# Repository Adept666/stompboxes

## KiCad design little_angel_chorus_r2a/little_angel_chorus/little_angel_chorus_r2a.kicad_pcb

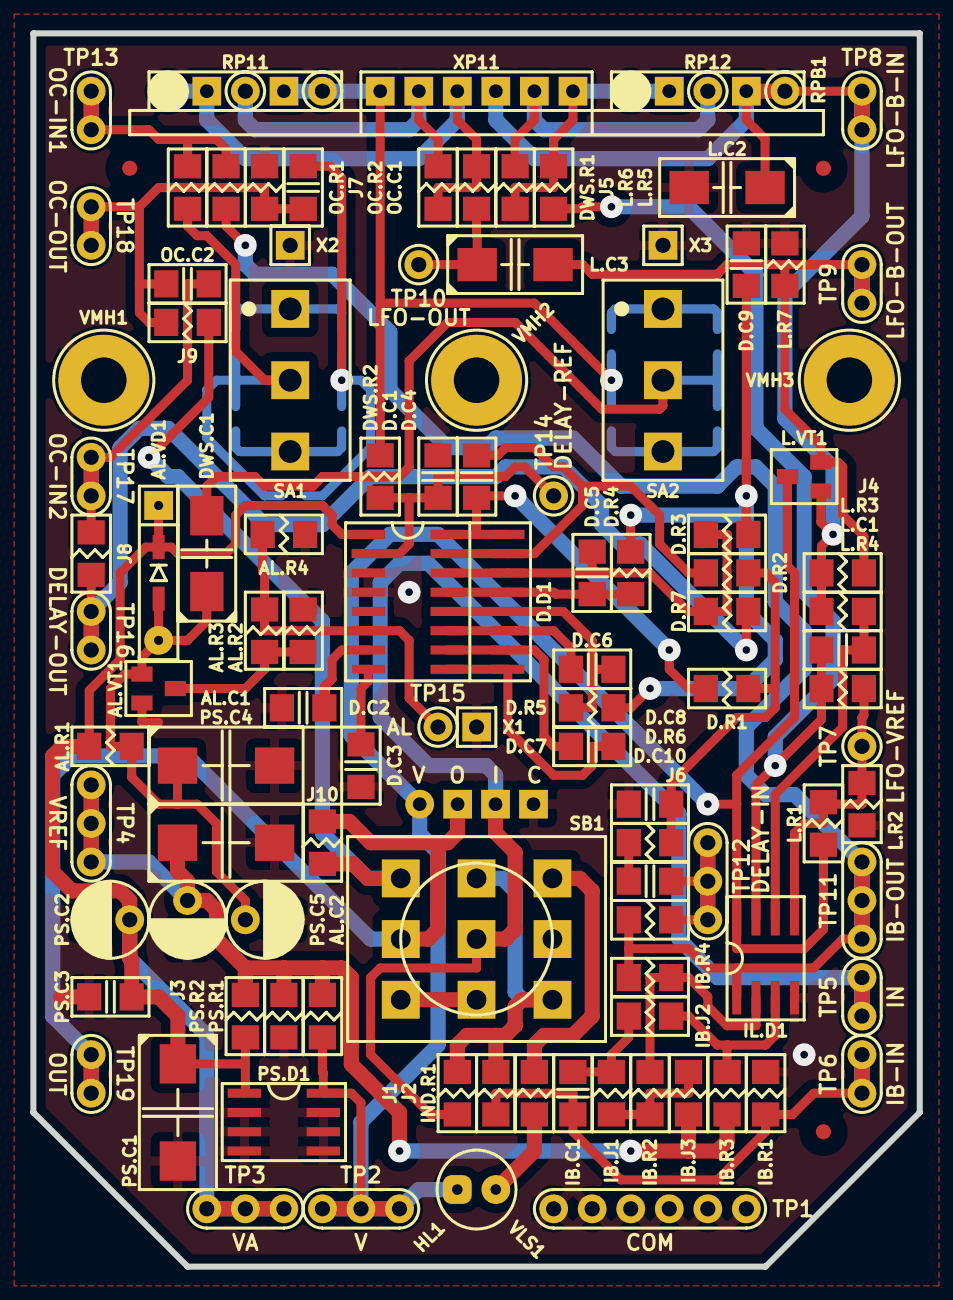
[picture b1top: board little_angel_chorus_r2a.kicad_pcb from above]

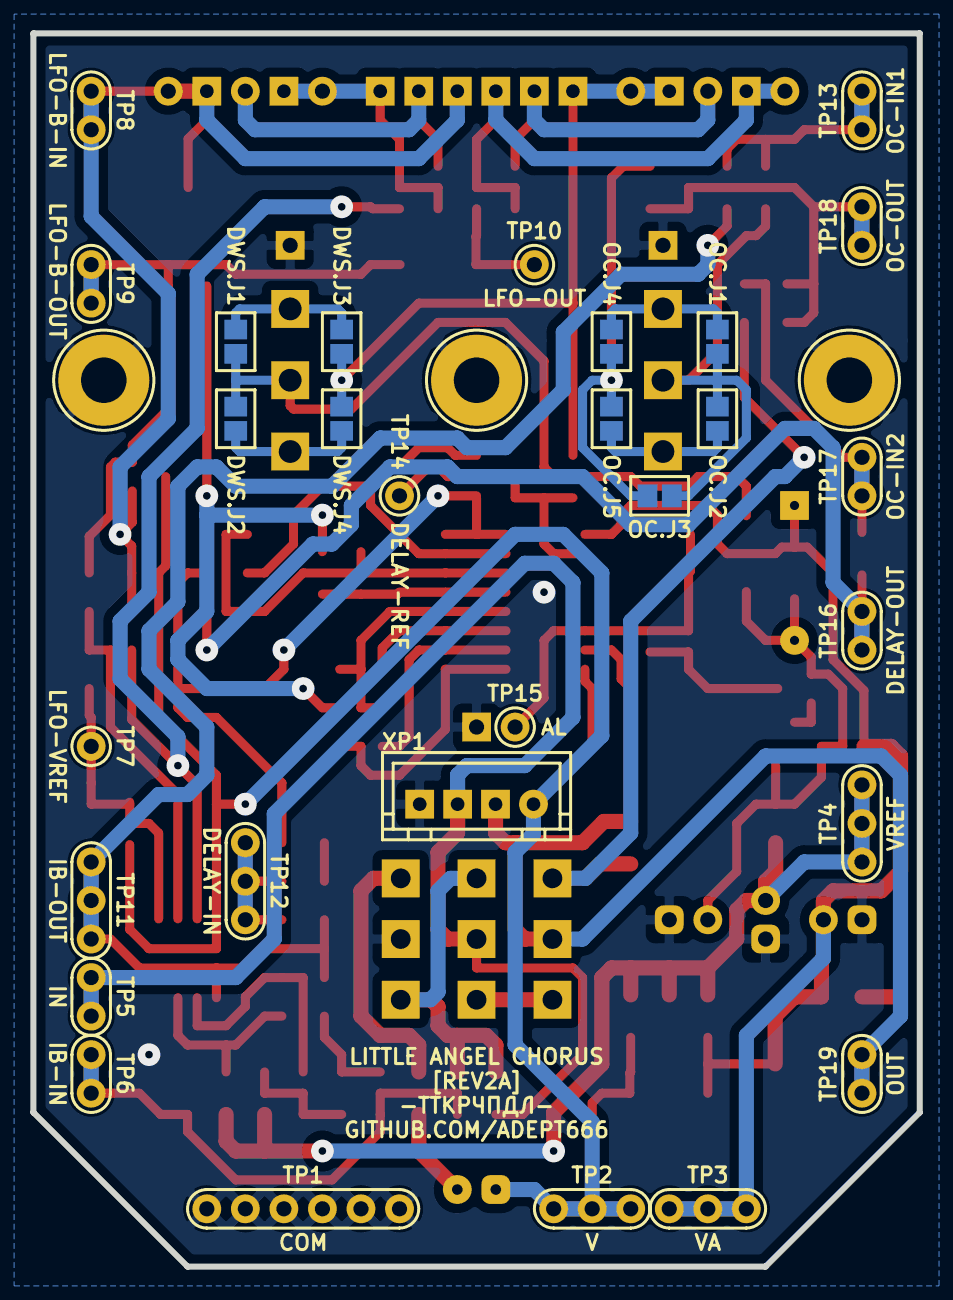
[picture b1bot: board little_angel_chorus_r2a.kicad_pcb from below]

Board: 2 copper layers, 58.4 x 81.3 mm, 118 parts (10 on the bottom side), 57 nets.

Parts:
AL.C1: 476; CP-CTSMD-D
AL.C2: 476; CP-RADIAL-D05.0-P02.0-CLS
AL.R1: 683; R-SM-1206
AL.R2: X; R-SM-1206
AL.R3: 101; R-SM-1206
AL.R4: 222; R-SM-1206
AL.VD1: 4148; P-SOD-123-OR-DO-35-V2
AL.VT1: 3904; P-SOT-23-B-E-C
D.C1: 105; C-SM-1206
D.C2, D.C3, D.C10: 104; C-SM-1206
D.C4, D.C8, D.C9: 332; C-SM-1206
D.C5: 102; C-SM-1206
D.C6, D.C7: 103; C-SM-1206
D.D1: 8970; P-SO-16-OR-SO-16W
D.R1, D.R2, D.R3, D.R4, D.R5, D.R6, D.R7: 103; R-SM-1206
DWS.C1: X; CP-CTSMD-C
DWS.J1: DWS.J1; J-SB-0805-2
DWS.J2: DWS.J2; J-SB-0805-2
DWS.J3: DWS.J3; J-SB-0805-2
DWS.J4: DWS.J4; J-SB-0805-2
DWS.R1: 0; R-SM-1206
DWS.R2: 333; R-SM-1206
HL1: FYL-5013UWC; LED-ROUND-05.0-UNI-SH-SPACER-PNL-5.3
IB.C1: 104; C-SM-1206
IB.J1: X; R-SM-1206
IB.J2, IB.J3: 0; R-SM-1206
IB.R1: 105; R-SM-1206
IB.R2, IB.R4: 223; R-SM-1206
IB.R3: 474; R-SM-1206
IL.D1: 5532; P-SO-08
IND.R1: 103; R-SM-1206
J1, J3, J4, J10: X; R-SM-1206
J2, J5, J6, J7, J8, J9: 0; R-SM-1206
L.C1: 103; C-SM-1206
L.C2, L.C3: 106; CP-CTSMD-C
L.R1: 104; R-SM-1206
L.R2: 473; R-SM-1206
L.R3, L.R4: 224; R-SM-1206
L.R5: 472; R-SM-1206
L.R6: 0; R-SM-1206
L.R7: 103; R-SM-1206
L.VT1: 3904; P-SOT-23-B-E-C
OC.C1, OC.C2: 104; C-SM-1206
OC.J1: OC.J1; J-SB-0805-2
OC.J2: OC.J2; J-SB-0805-2
OC.J3: OC.J3; J-SB-0805-2
OC.J4: OC.J4; J-SB-0805-2
OC.J5: OC.J5; J-SB-0805-2
OC.R1: 103; R-SM-1206
OC.R2: 104; R-SM-1206
PS.C1, PS.C4: 476; CP-CTSMD-D
PS.C2, PS.C5: 476; CP-RADIAL-D05.0-P02.0-CLS
PS.C3: 104; C-SM-1206
PS.D1: 78L05; P-SO-08-OUT-GND-GND-NC-NC-GND-GND-IN
PS.R1, PS.R2: 103; R-SM-1206
RPB1: B50K-B50K; RPB-1590N1-18-2x17-OR-2x1x17-1.6-PNL-7.4-2.8
SA1, SA2: X; SW-MTS-102-A2-2.5-PNL-6.0
SB1: PBS-24-302SP; SW-PBS-24-302SP-2.5-PNL-13.0
TP1: COM; TP-6-1.0-1.9
TP2: V; TP-3-1.0-1.9
TP3: VA; TP-3-1.0-1.9
TP4: VREF; TP-3-1.0-1.9
TP5: IN; TP-2-1.0-1.9
TP6: IB-IN; TP-2-1.0-1.9
TP7: LFO-VREF; TP-1-1.0-1.9
TP8: LFO-B-IN; TP-2-1.0-1.9
TP9: LFO-B-OUT; TP-2-1.0-1.9
TP10: LFO-OUT; TP-1-1.0-1.9
TP11: IB-OUT; TP-3-1.0-1.9
TP12: DELAY-IN; TP-3-1.0-1.9
TP13: OC-IN1; TP-2-1.0-1.9
TP14: DELAY-REF; TP-1-1.0-1.9
TP15: AL; TP-1-1.0-1.9
TP16: DELAY-OUT; TP-2-1.0-1.9
TP17: OC-IN2; TP-2-1.0-1.9
TP18: OC-OUT; TP-2-1.0-1.9
TP19: OUT; TP-2-1.0-1.9
VE1: 1590N1; 1590N1_A1
VFM1, VFM2, VFM3: 1.0; VFM-1.0-3.0-SL
VLS1: BR-12.7; VLS-BR
VMH1, VMH3: DI5M3x18; VMH-STA-DA5-PNL-3.0
VMH2: X; VMH-STA-DA5-PNL-3.0
X1: COM; CON-PAD-S-1.0-1.9
X2, X3: X; CON-PAD-S-1.0-1.9
XB1: 1590N1 Connector Board; XB-1590N1
XP1: B4B-XH-A; CON-XH-B4B-A

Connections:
/AL: AL.R3.2, AL.R4.2, D.D1.6, TP15.1
/CIR-IN: J1.2, J2.1, SB1.NC3, SB1.NO2
/CIR-OUT: J9.2, J10.1, SB1.NO1
/DELAY-IN: D.C10.2, J6.2, TP12.1
/DELAY-OUT: D.R7.2, J8.1, TP16.1
/DELAY-REF: D.C1.1, D.D1.2, DWS.R2.2, TP14.1
/DEPTH-IN: DWS.R1.1, J5.2, RPB1.11, RPB1.NC1
/IB-IN: IB.C1.1, IB.R1.2, J2.2, TP6.1
/IB-OUT: IB.R4.2, IL.D1.1, J6.1, J7.1, TP11.1
/IN: J1.1, SB1.COM2, TP5.1, XP1.3
/LED: IND.R1.1, SB1.NO3
/LFO-B-IN: J4.1, L.C2.+, L.R3.2, L.VT1.B, RPB1.23, RPB1.NC4, TP8.1
/LFO-B-OUT: J4.2, L.C3.-, L.R7.2, L.VT1.E, TP9.1
/LFO-OUT: J5.1, L.C3.+, TP10.1
/LFO-VREF: IL.D1.5, L.R1.1, L.R2.2, L.R4.1, TP7.1
/OC-IN1: J7.2, OC.R1.1, TP13.1
/OC-IN2: J8.2, OC.C2.1, TP17.1
/OC-OUT: J9.1, OC.C1.2, OC.C2.2, OC.R2.2, TP18.1
/OUT: J10.2, SB1.COM1, TP19.1, XP1.2
/WS: AL.C1.+, AL.C2.+, AL.R1.1, AL.VD1.A, AL.VT1.B, DWS.C1.+
COM: AL.C1.-, AL.C2.-, AL.R2.1, AL.R4.1, AL.VT1.E, D.C1.2, D.C2.1, D.C3.1, D.C8.1, D.C9.2, D.D1.3, D.D1.4, IB.R1.1, IL.D1.4, L.C2.-, L.R2.1, L.R7.1, OC.R2.1, PS.C1.-, PS.C2.-, PS.C3.2, PS.C4.-, PS.C5.-, PS.D1.GND, PS.D1.NC, PS.R2.1, SB1.COM3, TP1.1, VMH1.0, VMH2.0, VMH3.0, X1.1, X2.1, X3.1, XP1.4
unnamed: AL.R2.2, AL.R3.1, AL.VT1.C
unnamed: D.C2.2, D.D1.7
unnamed: D.C3.2, D.D1.8
unnamed: D.C4.1, D.D1.16, D.R1.1
unnamed: D.C4.2, D.D1.15, D.R2.1
unnamed: D.C5.1, D.D1.14, D.R3.1, D.R7.1
unnamed: D.C5.2, D.D1.13, D.R4.1
unnamed: D.C6.1, D.D1.12, D.R5.1
unnamed: D.C6.2, D.D1.11
unnamed: D.C7.1, D.D1.10
unnamed: D.C7.2, D.D1.9
unnamed: D.C8.2, D.R1.2, D.R2.2, D.R6.1
unnamed: D.C9.1, D.R3.2, D.R4.2, D.R5.2
unnamed: D.C10.1, D.R6.2
unnamed: DWS.C1.-, DWS.J1.1, DWS.J2.1, SA2.COM
unnamed: DWS.J1.2, DWS.J3.1, SA2.NC
unnamed: DWS.J2.2, DWS.J4.1, SA2.NO
unnamed: DWS.J3.2, DWS.J4.2, DWS.R2.1, RPB1.13, RPB1.NC2
unnamed: DWS.R1.2, RPB1.12
unnamed: HL1.C, IND.R1.2
unnamed: IB.C1.2, IB.J1.1, IB.J2.1
unnamed: IB.J1.2, IB.J3.2, IB.R2.1
unnamed: IB.J2.2, IB.R3.2, IL.D1.3
unnamed: IB.R2.2, IB.R4.1, IL.D1.2
unnamed: IL.D1.6, L.C1.1, L.R3.1
unnamed: IL.D1.7, L.C1.2, L.R4.2, L.R5.1
unnamed: L.R5.2, L.R6.1, RPB1.21, RPB1.NC3
unnamed: L.R6.2, RPB1.22
unnamed: OC.C1.1, OC.J3.2, OC.J4.2, OC.J5.2
unnamed: OC.J1.1, OC.J2.1, OC.J3.1, OC.R1.2, SA1.COM
unnamed: OC.J1.2, OC.J4.1, SA1.NC
unnamed: OC.J2.2, OC.J5.1, SA1.NO
unnamed: SB1.NC1, SB1.NC2
V: HL1.A, IL.D1.8, L.R1.2, L.VT1.C, PS.D1.IN, PS.R1.2, TP2.1, XP1.1
VA: AL.R1.2, AL.VD1.C, D.D1.1, J3.1, PS.C1.+, PS.C2.+, PS.C3.1, PS.D1.OUT, TP3.1
VREF: IB.J3.1, IB.R3.1, J3.2, PS.C4.+, PS.C5.+, PS.R1.1, PS.R2.2, TP4.1

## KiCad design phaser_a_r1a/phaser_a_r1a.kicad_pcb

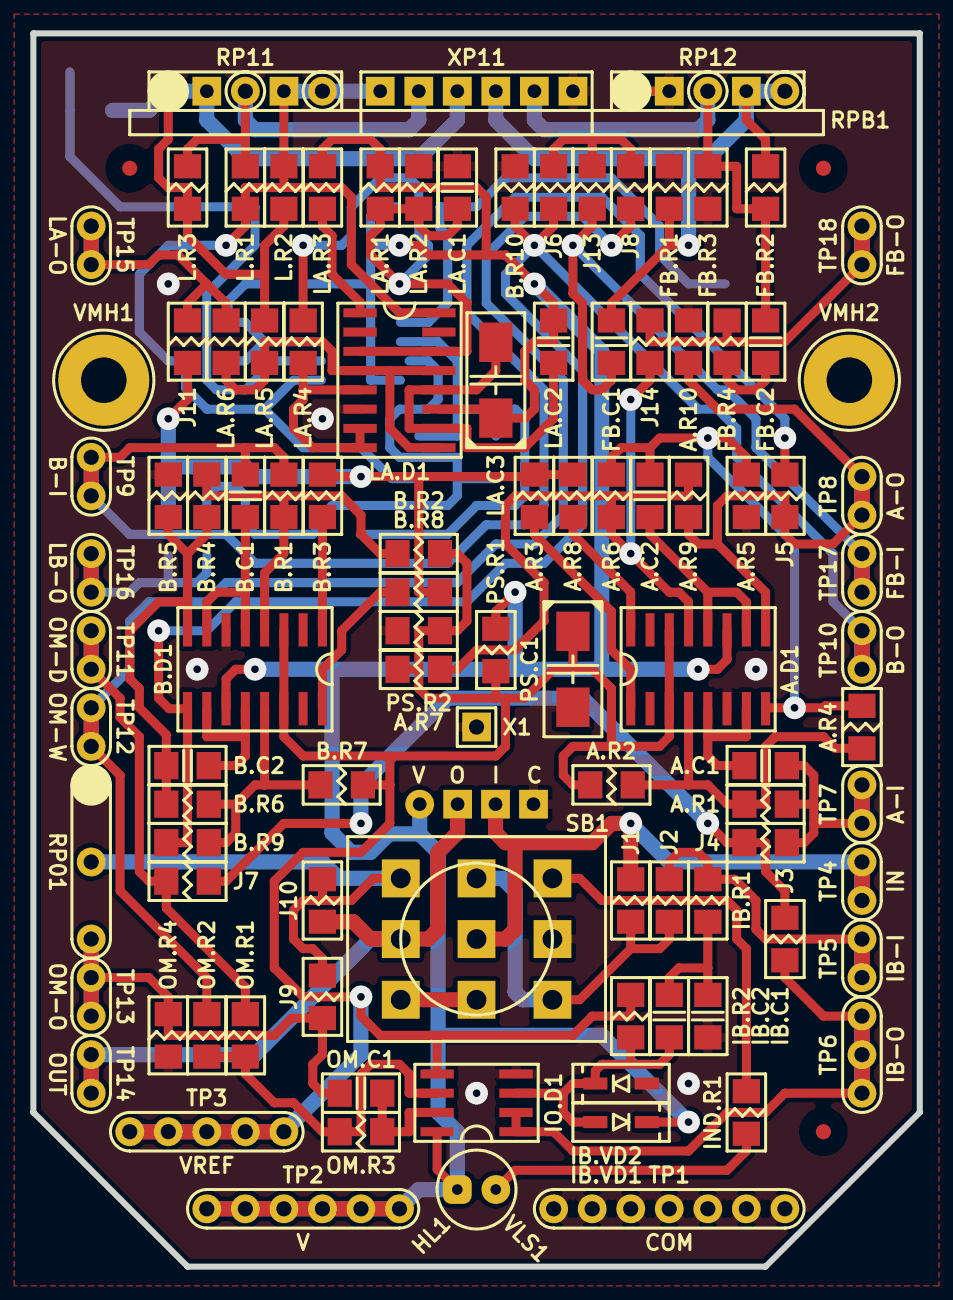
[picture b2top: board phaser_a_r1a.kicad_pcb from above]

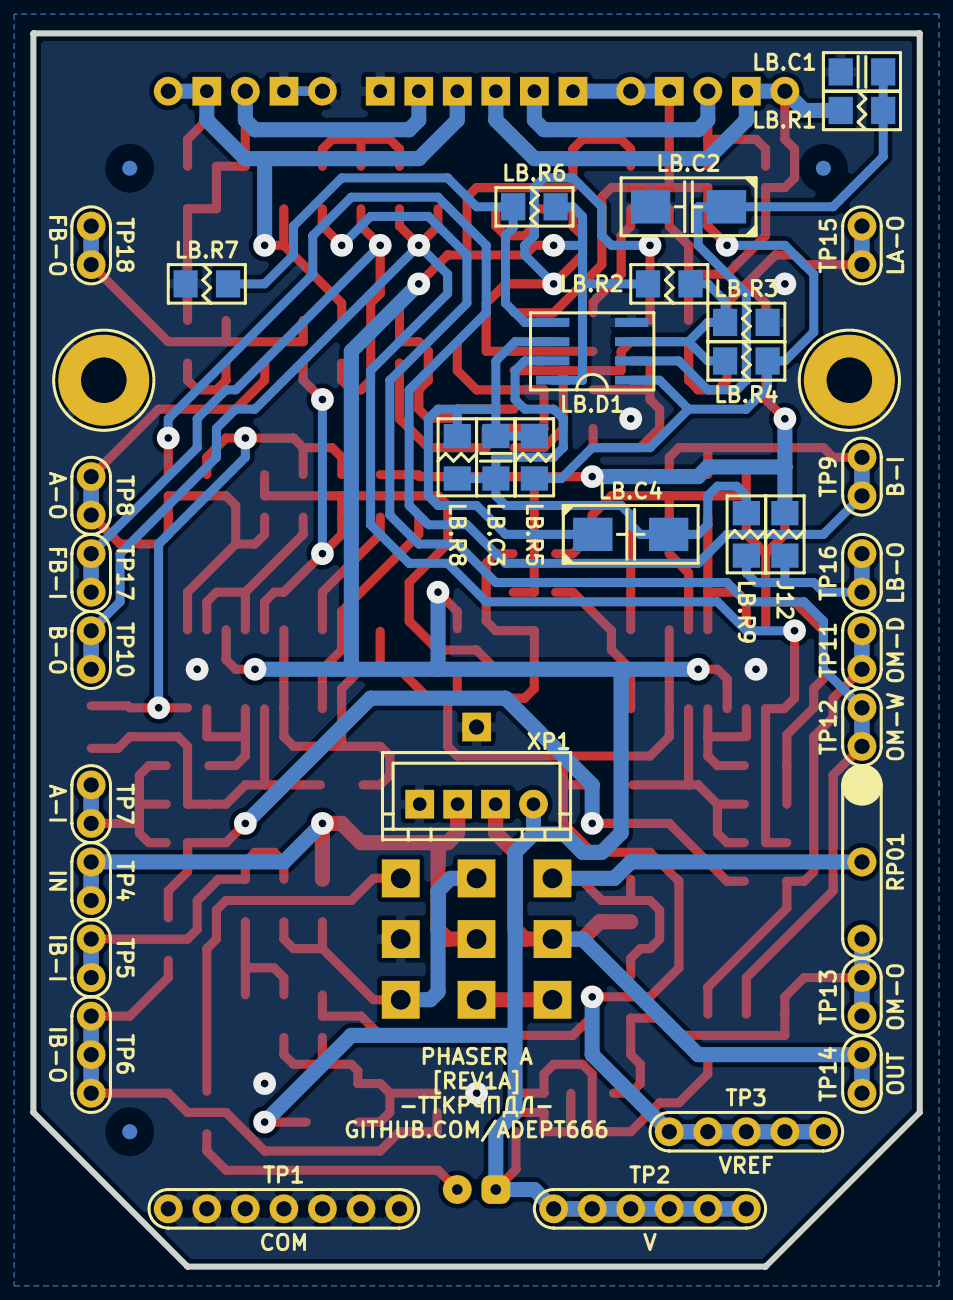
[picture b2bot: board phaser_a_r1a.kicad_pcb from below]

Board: 2 copper layers, 58.4 x 81.3 mm, 121 parts (16 on the bottom side), 60 nets.

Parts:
A.C1, A.C2: 332; C-SM-1206
A.D1: 13700; P-SO-16
A.R1, A.R4, A.R6, A.R9: 273; R-SM-1206
A.R2, A.R7: 182; R-SM-1206
A.R3, A.R8: 0; R-SM-1206
A.R5, A.R10: 103; R-SM-1206
B.C1, B.C2: 332; C-SM-1206
B.D1: 13700; P-SO-16
B.R1, B.R4, B.R6, B.R9: 273; R-SM-1206
B.R2, B.R7: 182; R-SM-1206
B.R3, B.R8: 0; R-SM-1206
B.R5, B.R10: 103; R-SM-1206
FB.C1, FB.C2: 105; C-SM-1206
FB.R1, FB.R3: X; R-SM-1206
FB.R2, FB.R4: 273; R-SM-1206
HL1: FYL-5013UWC; LED-ROUND-05.0-UNI-SH-SPACER-PNL-5.3
IB.C1: 101; C-SM-1206
IB.C2: 103; C-SM-1206
IB.R1: 102; R-SM-1206
IB.R2: 474; R-SM-1206
IB.VD1, IB.VD2: 4148; P-SOD-123
IND.R1: 103; R-SM-1206
IO.D1: 4558; P-SO-08
J1, J10, J12: X; R-SM-1206
J2, J3, J4, J5, J6, J7, J8, J9, J11, J13, J14: 0; R-SM-1206
L.R1, L.R2: X; R-SM-1206
L.R3: 0; R-SM-1206
LA.C1: 473; C-SM-1206
LA.C2: 335; C-SM-1206
LA.C3: X; CP-CTSMD-C
LA.D1: 13700; P-SO-16
LA.R1, LA.R3: 274; R-SM-1206
LA.R2: 104; R-SM-1206
LA.R4, LA.R6: 103; R-SM-1206
LA.R5: 472; R-SM-1206
LB.C1, LB.C3: X; C-SM-1206
LB.C2, LB.C4: X; CP-CTSMD-C
LB.D1: X; P-SO-08
LB.R1, LB.R2, LB.R3, LB.R4, LB.R5, LB.R6, LB.R7, LB.R8, LB.R9: X; R-SM-1206
OM.C1: 105; C-SM-1206
OM.R1, OM.R2: 273; R-SM-1206
OM.R3: 153; R-SM-1206
OM.R4: 154; R-SM-1206
PS.C1: 106; CP-CTSMD-C
PS.R1, PS.R2: 103; R-SM-1206
RP01: X; RP-EXTERNAL
RPB1: C500K-C500K; RPB-1590N1-18-2x17-OR-2x1x17-1.6-PNL-7.4-2.8
SB1: PBS-24-302SP; SW-PBS-24-302SP-2.5-PNL-13.0
TP1: COM; TP-7-1.0-1.9
TP2: V; TP-6-1.0-1.9
TP3: VREF; TP-5-1.0-1.9
TP4: IN; TP-2-1.0-1.9
TP5: IB-I; TP-2-1.0-1.9
TP6: IB-O; TP-3-1.0-1.9
TP7: A-I; TP-2-1.0-1.9
TP8: A-O; TP-2-1.0-1.9
TP9: B-I; TP-2-1.0-1.9
TP10: B-O; TP-2-1.0-1.9
TP11: OM-D; TP-2-1.0-1.9
TP12: OM-W; TP-2-1.0-1.9
TP13: OM-O; TP-2-1.0-1.9
TP14: OUT; TP-2-1.0-1.9
TP15: LA-O; TP-2-1.0-1.9
TP16: LB-O; TP-2-1.0-1.9
TP17: FB-I; TP-2-1.0-1.9
TP18: FB-O; TP-2-1.0-1.9
VE1: 1590N1; 1590N1_A1
VFM1, VFM2, VFM3: 1.0; VFM-1.0-3.0-DL
VLS1: BR-12.7; VLS-BR
VMH1, VMH2: DI5M3x18; VMH-STA-DA5-PNL-3.0
X1: COM; CON-PAD-S-1.0-1.9
XB1: 1590N1 Connector Board; XB-1590N1
XP1: B4B-XH-A; CON-XH-B4B-A

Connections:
/A-IN: A.C1.1, A.R1.1, J4.2, TP7.1
/A-OUT: A.D1.9, A.R9.2, A.R10.1, J5.1, TP8.1
/B-IN: B.C1.1, B.R1.1, J5.2, TP9.1
/B-OUT: B.D1.9, B.R9.2, B.R10.1, J6.1, TP10.1
/CIR-IN: J1.2, J2.1, SB1.NC3, SB1.NO2
/CIR-OUT: J9.2, J10.1, RP01.2, SB1.NO1
/DRY: J3.2, J4.1, J7.1
/FB: A.D1.13, A.R6.2, A.R7.1, A.R9.1, J14.2
/FB-IN: FB.C1.1, J13.2, TP17.1
/FB-OUT: FB.R4.2, J14.1, TP18.1
/IB-IN: IB.R1.1, J2.2, TP5.1
/IB-OUT: IO.D1.1, IO.D1.2, J3.1, TP6.1
/IN: J1.1, SB1.COM2, TP4.1, XP1.3
/LED: IND.R1.1, SB1.NO3
/LFO: A.R3.1, A.R8.1, B.R3.1, B.R8.1, J11.2, J12.2
/LFOA-OUT: J11.1, LA.R6.2, TP15.1
/LFOB-OUT: J12.1, LB.R9.2, TP16.1
/OM-INDRY: J7.2, OM.R1.2, TP11.1
/OM-INWET: J8.2, OM.R2.1, TP12.1
/OM-OUT: J9.1, OM.C1.2, OM.R4.2, RP01.3, TP13.1
/OUT: J10.2, SB1.COM1, TP14.1, XP1.2
/RP11-1: L.R2.2, L.R3.2, LA.R5.1, LB.R1.2, RPB1.11, RPB1.NC1
/RP11-2: L.R1.2, L.R3.1, RPB1.12
/RP11-3: L.R1.1, L.R2.1, LA.D1.16, LB.D1.1, LB.R4.2, LB.R5.1, RPB1.13, RPB1.NC2
/WET: J6.2, J8.1, J13.1
COM: A.D1.6, A.R5.2, A.R10.2, B.D1.6, B.R5.2, B.R10.2, FB.R1.1, FB.R3.1, IB.C1.2, IB.VD2.A, IO.D1.4, LA.C1.2, LA.D1.6, LA.R2.1, LB.C1.1, LB.C2.-, LB.D1.4, LB.R3.1, LB.R7.1, OM.R4.1, PS.C1.-, PS.R2.1, RP01.1, RPB1.21, RPB1.NC3, SB1.COM3, TP1.1, VMH1.0, VMH2.0, X1.1, XP1.4
unnamed: A.C1.2, A.D1.5, A.D1.7
unnamed: A.C2.1, A.D1.8, A.R4.2, A.R5.1, A.R6.1
unnamed: A.C2.2, A.D1.10, A.D1.12
unnamed: A.D1.1, A.R3.2
unnamed: A.D1.4, A.R1.2, A.R2.1, A.R4.1
unnamed: A.D1.16, A.R8.2
unnamed: B.C1.2, B.D1.5, B.D1.7
unnamed: B.C2.1, B.D1.8, B.R4.2, B.R5.1, B.R6.1
unnamed: B.C2.2, B.D1.10, B.D1.12
unnamed: B.D1.1, B.R3.2
unnamed: B.D1.4, B.R1.2, B.R2.1, B.R4.1
unnamed: B.D1.13, B.R6.2, B.R7.1, B.R9.1
unnamed: B.D1.16, B.R8.2
unnamed: FB.C1.2, FB.R1.2, FB.R2.2, RPB1.23, RPB1.NC4
unnamed: FB.C2.1, FB.R2.1, FB.R3.2, RPB1.22
unnamed: FB.C2.2, FB.R4.1
unnamed: HL1.C, IND.R1.2
unnamed: IB.C1.1, IB.C2.1, IB.R1.2
unnamed: IB.C2.2, IB.R2.2, IB.VD1.A, IB.VD2.C, IO.D1.3
unnamed: IO.D1.6, OM.R1.1, OM.R2.2, OM.R3.1
unnamed: IO.D1.7, OM.C1.1, OM.R3.2
unnamed: LA.C1.1, LA.D1.3, LA.D1.14, LA.R1.1, LA.R2.2, LA.R4.1
unnamed: LA.C2.2, LA.C3.-, LA.D1.10, LA.D1.12
unnamed: LA.D1.1, LA.R3.1
unnamed: LA.D1.5, LA.D1.7, LA.D1.8, LA.R4.2
unnamed: LA.D1.4, LA.D1.9, LA.D1.13, LA.R5.2, LA.R6.1
unnamed: LB.C1.2, LB.C2.+, LB.D1.2, LB.R1.1
unnamed: LB.C3.1, LB.C4.+, LB.D1.6, LB.R5.2, LB.R8.1
unnamed: LB.C3.2, LB.C4.-, LB.D1.7, LB.R8.2, LB.R9.1
unnamed: LB.D1.3, LB.R2.2, LB.R3.2, LB.R4.1
unnamed: LB.D1.5, LB.R6.1, LB.R7.2
unnamed: SB1.NC1, SB1.NC2
V: A.D1.11, B.D1.11, HL1.A, IB.VD1.C, IO.D1.8, LA.C2.1, LA.C3.+, LA.D1.11, LA.R1.2, LA.R3.2, LB.D1.8, LB.R2.1, LB.R6.2, PS.R1.2, TP2.1, XP1.1
VREF: A.D1.3, A.D1.14, A.R2.2, A.R7.2, B.D1.3, B.D1.14, B.R2.2, B.R7.2, IB.R2.1, IO.D1.5, PS.C1.+, PS.R1.1, PS.R2.2, TP3.1

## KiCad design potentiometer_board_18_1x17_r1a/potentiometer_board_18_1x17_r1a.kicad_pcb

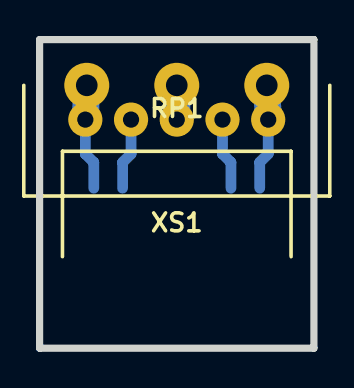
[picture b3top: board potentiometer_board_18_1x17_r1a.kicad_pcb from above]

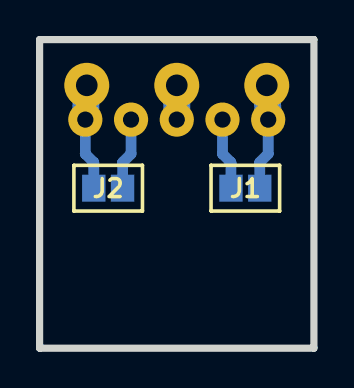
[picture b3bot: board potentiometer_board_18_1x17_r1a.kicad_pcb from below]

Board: 2 copper layers, 15.2 x 17.1 mm, 4 parts (2 on the bottom side), 5 nets.

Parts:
J1: J1; J-SB-0805-2
J2: J2; J-SB-0805-2
RP1: 16/17; RP-PDB181-K-20-P-CIRCULAR
XS1: PBS-05R; CON-PBS-05R-CIRCULAR

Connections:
unnamed: J1.1, RP1.3, XS1.1
unnamed: J1.2, XS1.2
unnamed: J2.1, XS1.4
unnamed: J2.2, RP1.1, XS1.5
unnamed: RP1.2, XS1.3

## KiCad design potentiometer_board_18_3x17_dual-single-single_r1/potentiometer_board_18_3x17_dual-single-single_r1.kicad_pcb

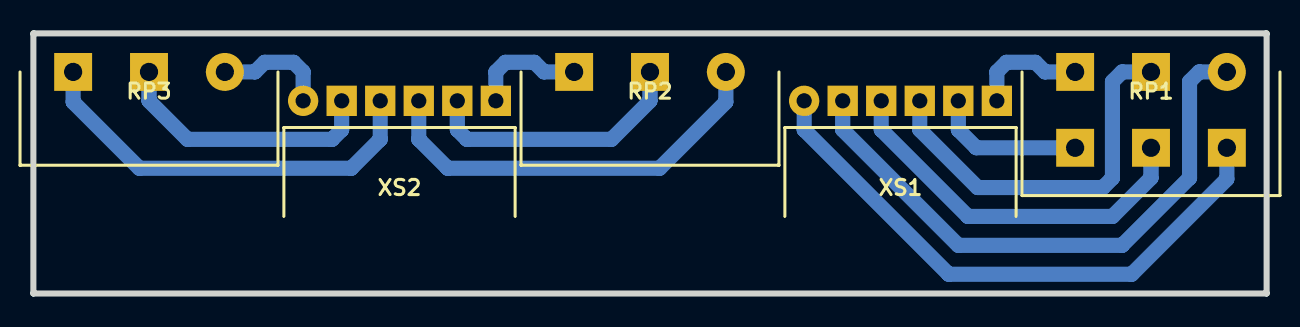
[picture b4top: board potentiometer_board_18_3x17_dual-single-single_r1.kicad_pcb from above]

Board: 2 copper layers, 81.3 x 17.1 mm, 5 parts (0 on the bottom side), 12 nets.

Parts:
RP1: RP1: DUAL 16/17; RP-PDB182-K-20-P
RP2: RP2: 16/17; RP-PDB181-K-20-P
RP3: RP3: 16/17; RP-PDB181-K-20-P
XS1, XS2: PBS-06R; CON-PBS-06R

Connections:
unnamed: RP1.1, XS1.2
unnamed: RP1.2, XS1.4
unnamed: RP1.3, XS1.6
unnamed: RP1.4, XS1.1
unnamed: RP1.5, XS1.3
unnamed: RP1.6, XS1.5
unnamed: RP2.1, XS2.4
unnamed: RP2.2, XS2.5
unnamed: RP2.3, XS2.6
unnamed: RP3.1, XS2.1
unnamed: RP3.2, XS2.2
unnamed: RP3.3, XS2.3

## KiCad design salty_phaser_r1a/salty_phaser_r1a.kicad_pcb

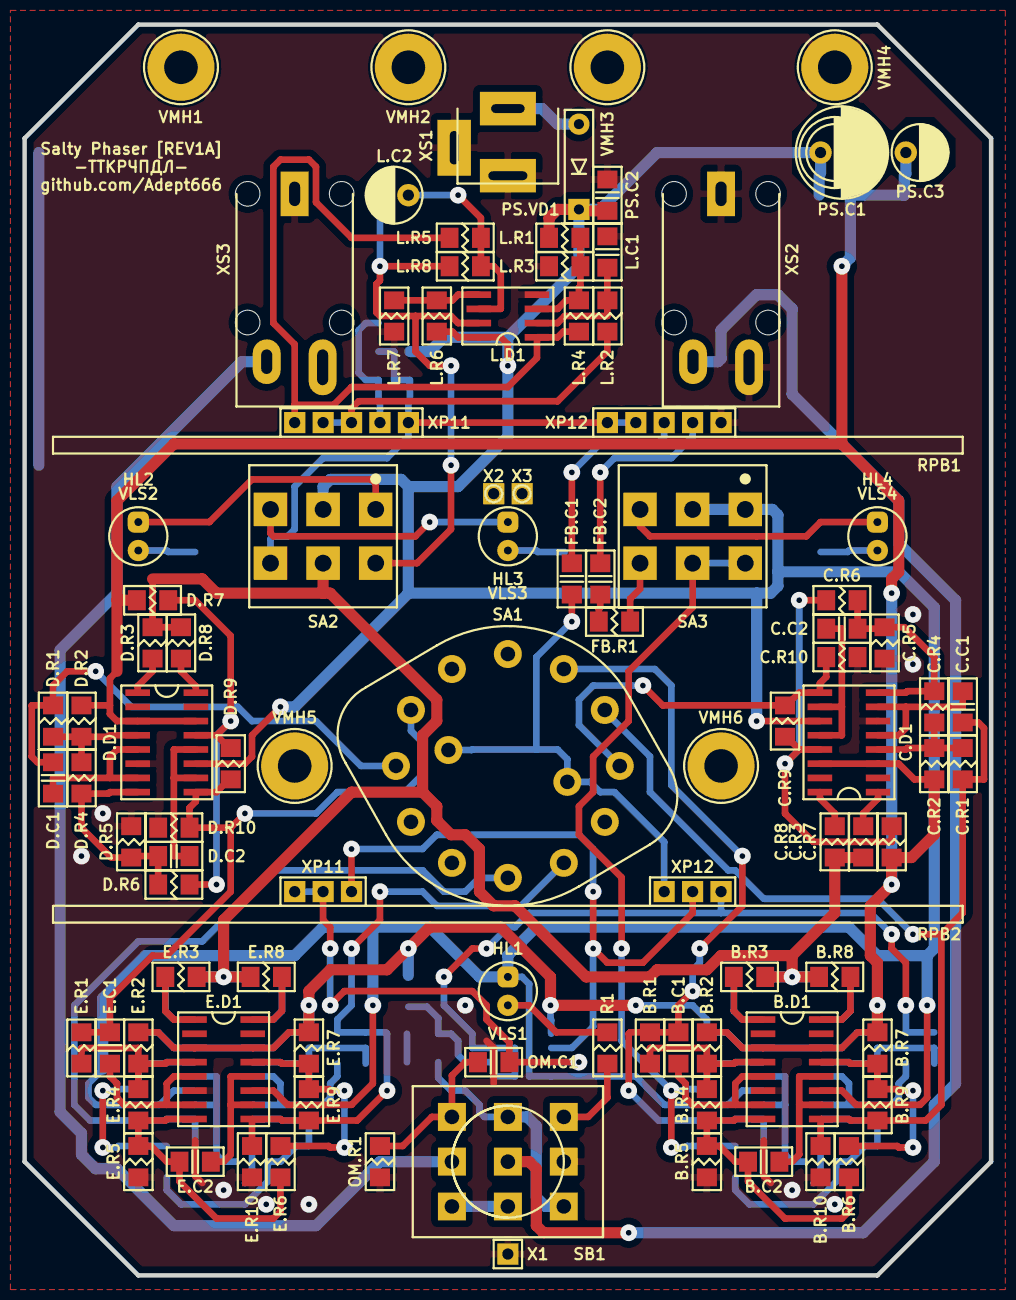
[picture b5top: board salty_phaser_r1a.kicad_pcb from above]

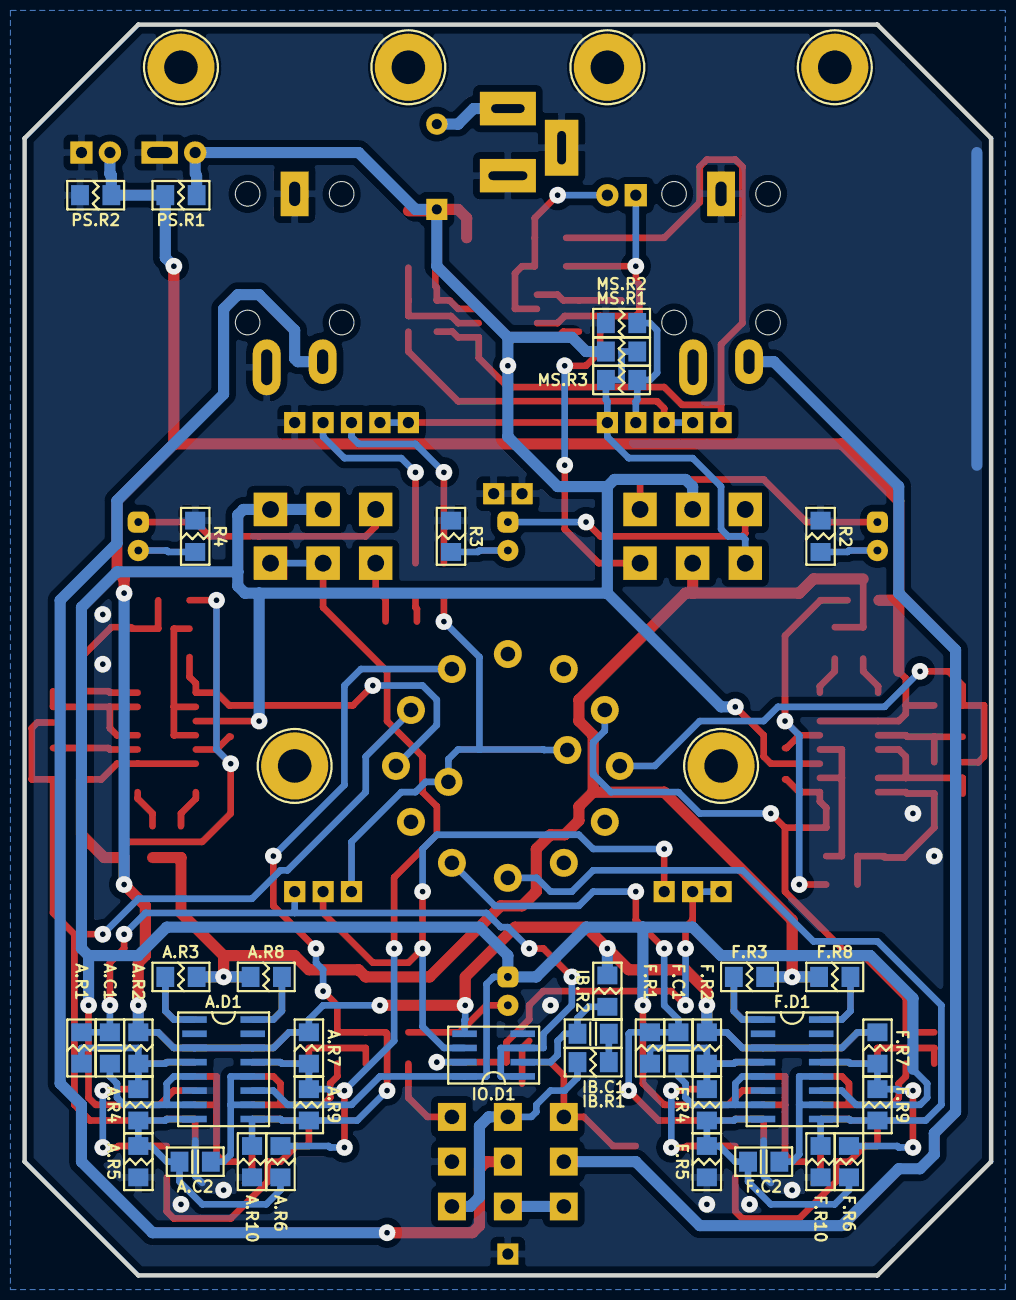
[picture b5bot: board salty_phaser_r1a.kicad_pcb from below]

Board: 2 copper layers, 86.4 x 111.8 mm, 138 parts (38 on the bottom side), 85 nets.

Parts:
A.C1, A.C2: X; C-SM-1206
A.D1: X; P-SO-16
A.R1, A.R2, A.R3, A.R4, A.R5, A.R6, A.R7, A.R8, A.R9, A.R10: X; R-SM-1206
B.C1, B.C2: X; C-SM-1206
B.D1: X; P-SO-16
B.R1, B.R2, B.R3, B.R4, B.R5, B.R6, B.R7, B.R8, B.R9, B.R10: X; R-SM-1206
C.C1, C.C2: 332; C-SM-1206
C.D1: 13700; P-SO-16
C.R1, C.R4, C.R6, C.R9: 273; R-SM-1206
C.R2, C.R7: 182; R-SM-1206
C.R3, C.R5, C.R8, C.R10: 103; R-SM-1206
D.C1, D.C2: 332; C-SM-1206
D.D1: 13700; P-SO-16
D.R1, D.R4, D.R6, D.R9: 273; R-SM-1206
D.R2, D.R7: 182; R-SM-1206
D.R3, D.R5, D.R8, D.R10: 103; R-SM-1206
E.C1, E.C2: X; C-SM-1206
E.D1: X; P-SO-16
E.R1, E.R2, E.R3, E.R4, E.R5, E.R6, E.R7, E.R8, E.R9, E.R10: X; R-SM-1206
F.C1, F.C2: X; C-SM-1206
F.D1: X; P-SO-16
F.R1, F.R2, F.R3, F.R4, F.R5, F.R6, F.R7, F.R8, F.R9, F.R10: X; R-SM-1206
FB.C1, FB.C2: X; C-SM-1206
FB.R1: X; R-SM-1206
HL1: FYL-5013UWC; LED-ROUND-05.0-UNI-SH-SPACER-PNL-5.3
HL2, HL3, HL4: X; LED-ROUND-05.0-UNI-SH-SPACER-PNL-5.3
IB.C1: 472; C-SM-1206
IB.R1: 103; R-SM-1206
IB.R2: 105; R-SM-1206
IO.D1: 4558; P-SO-08
L.C1: 474; C-SM-1206
L.C2: 475; CP-RADIAL-D05.0-P02.0-CLS
L.D1: 4558; P-SO-08
L.R1, L.R3, L.R4: 364; R-SM-1206
L.R2: 154; R-SM-1206
L.R5, L.R6, L.R8: 103; R-SM-1206
L.R7: 622; R-SM-1206
MS.R1: 331; R-SM-1206
MS.R2: 680; R-SM-1206
MS.R3: 470; R-SM-1206
OM.C1: 473; C-SM-1206
OM.R1: X; R-SM-1206
PS.C1: 107; CP-RADIAL-D05.0-P02.0-CLS-OR-D06.3-P02.5-OR-D08.0-P03.5-CLS
PS.C2: 104; C-SM-1206
PS.C3: 106; CP-RADIAL-D05.0-P02.0-CLS
PS.R1, PS.R2: 103; R-SM-1206
PS.VD1: 5817; P-DO-41
R1: 103; R-SM-1206
R2, R3, R4: X; R-SM-1206
RPB1: B500K-A1K-B100K; RPB-1590BB-18-3x17-1.5-PNL-7.4-2.8
RPB2: X; RPB-1590BB-18-2x17-1.5-PNL-7.4-2.8
SA1: X; SW-RBS-1-2P6W-VP-PNL-9.5
SA2: MTS-202-A2; SW-MTS-202-A2-3.0-PNL-6.0
SA3: X; SW-MTS-202-A2-3.0-PNL-6.0
SB1: PBS-24-302SP; SW-PBS-24-302SP-2.5-PNL-13.0
VE1: 1590BB; 1590BB_B1
VLS1: BR-12.7; VLS-BR
VLS2, VLS3, VLS4: X; VLS-BR
VMH1, VMH2, VMH3, VMH4, VMH5, VMH6: DI5M3x18; VMH-STA-DA5-PNL-3.0
X1, X2: COM; CON-PAD-S-1.0-1.9
X3: X; CON-PAD-S-1.0-1.9
XS1: DC-005; CON-DC-005
XS2, XS3: PJ-309; CON-ST-008X-04-OR-ST-008X-05

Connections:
/DRY: A.C1.1, A.R1.1, IO.D1.1, IO.D1.3, RPB2.31
/FB: A.D1.13, A.R6.2, A.R7.1, A.R9.1, SA3.COM2, SA3.NC2
/FB-ON: FB.R1.2, SA3.NO2
/IN-CIR: IB.R1.1, SB1.NC3, SB1.NO2
/IN-CON: SB1.COM2, XS2.T
/LED: R1.1, SB1.NO3
/LED-FB: HL4.A, SA3.NO1
/LED-RATE: HL3.A, SA2.NO1
/LED-SPEED: HL2.A, SA2.NC1
/LFO: A.R3.1, A.R8.1, B.R3.1, B.R8.1, C.R3.1, C.R8.1, D.R3.1, D.R8.1, E.R3.1, E.R8.1, F.R3.1, F.R8.1, SA2.COM2
/LFO-AUTO: L.C2.-, L.D1.7, L.R8.2, SA2.NC2
/LFO-MANUAL: MS.R1.1, MS.R3.2, RPB1.22, RPB1.23, SA2.NO2
/OUT2: A.D1.9, A.R9.2, A.R10.1, B.C1.1, B.R1.1, SA1.1-1
/OUT4: B.D1.9, B.R9.2, B.R10.1, C.C1.1, C.R1.1, SA1.1-2
/OUT6: C.D1.9, C.R9.2, C.R10.1, D.C1.1, D.R1.1, SA1.1-3, SA1.2-3
/OUT8: D.D1.9, D.R9.2, D.R10.1, E.C1.1, E.R1.1, SA1.2-4
/OUT10: E.D1.9, E.R9.2, E.R10.1, F.C1.1, F.R1.1, SA1.1-5
/OUT12: F.D1.9, F.R9.2, F.R10.1, SA1.1-6
/OUT-CIR: OM.C1.2, OM.R1.2, SB1.NO1
/OUT-CON: SB1.COM1, XS3.T
/WET: FB.C1.1, RPB2.33, SA1.COM1, SA1.COM2
COM: A.D1.6, A.R5.2, A.R10.2, B.D1.6, B.R5.2, B.R10.2, C.D1.6, C.R5.2, C.R10.2, D.D1.6, D.R5.2, D.R10.2, E.D1.6, E.R5.2, E.R10.2, F.D1.6, F.R5.2, F.R10.2, IO.D1.4, L.C1.1, L.D1.4, L.R3.1, L.R7.1, MS.R2.1, OM.R1.1, PS.C1.-, PS.C2.2, PS.C3.-, PS.R2.1, R2.1, R3.1, R4.1, RPB1.31, SB1.COM3, VMH1.0, VMH2.0, VMH3.0, VMH4.0, X1.1, X2.1, X3.1, XS1.C, XS1.SN, XS2.R/TN, XS2.S, XS3.S
unnamed: A.C1.2, A.D1.5, A.D1.7
unnamed: A.C2.1, A.D1.8, A.R4.2, A.R5.1, A.R6.1
unnamed: A.C2.2, A.D1.10, A.D1.12
unnamed: A.D1.1, A.R3.2
unnamed: A.D1.4, A.R1.2, A.R2.1, A.R4.1
unnamed: A.D1.16, A.R8.2
unnamed: B.C1.2, B.D1.5, B.D1.7
unnamed: B.C2.1, B.D1.8, B.R4.2, B.R5.1, B.R6.1
unnamed: B.C2.2, B.D1.10, B.D1.12
unnamed: B.D1.1, B.R3.2
unnamed: B.D1.4, B.R1.2, B.R2.1, B.R4.1
unnamed: B.D1.13, B.R6.2, B.R7.1, B.R9.1
unnamed: B.D1.16, B.R8.2
unnamed: C.C1.2, C.D1.5, C.D1.7
unnamed: C.C2.1, C.D1.8, C.R4.2, C.R5.1, C.R6.1
unnamed: C.C2.2, C.D1.10, C.D1.12
unnamed: C.D1.1, C.R3.2
unnamed: C.D1.4, C.R1.2, C.R2.1, C.R4.1
unnamed: C.D1.13, C.R6.2, C.R7.1, C.R9.1
unnamed: C.D1.16, C.R8.2
unnamed: D.C1.2, D.D1.5, D.D1.7
unnamed: D.C2.1, D.D1.8, D.R4.2, D.R5.1, D.R6.1
unnamed: D.C2.2, D.D1.10, D.D1.12
unnamed: D.D1.1, D.R3.2
unnamed: D.D1.4, D.R1.2, D.R2.1, D.R4.1
unnamed: D.D1.13, D.R6.2, D.R7.1, D.R9.1
unnamed: D.D1.16, D.R8.2
unnamed: E.C1.2, E.D1.5, E.D1.7
unnamed: E.C2.1, E.D1.8, E.R4.2, E.R5.1, E.R6.1
unnamed: E.C2.2, E.D1.10, E.D1.12
unnamed: E.D1.1, E.R3.2
unnamed: E.D1.4, E.R1.2, E.R2.1, E.R4.1
unnamed: E.D1.13, E.R6.2, E.R7.1, E.R9.1
unnamed: E.D1.16, E.R8.2
unnamed: F.C1.2, F.D1.5, F.D1.7
unnamed: F.C2.1, F.D1.8, F.R4.2, F.R5.1, F.R6.1
unnamed: F.C2.2, F.D1.10, F.D1.12
unnamed: F.D1.1, F.R3.2
unnamed: F.D1.4, F.R1.2, F.R2.1, F.R4.1
unnamed: F.D1.13, F.R6.2, F.R7.1, F.R9.1
unnamed: F.D1.16, F.R8.2
unnamed: FB.C1.2, RPB1.33
unnamed: FB.C2.1, RPB1.32
unnamed: FB.C2.2, FB.R1.1
unnamed: HL1.C, R1.2
unnamed: HL2.C, R2.2
unnamed: HL3.C, R3.2
unnamed: HL4.C, R4.2
unnamed: IB.C1.1, IB.R1.2
unnamed: IB.C1.2, IB.R2.2, IO.D1.2
unnamed: IO.D1.6, RPB2.11, RPB2.32
unnamed: IO.D1.7, OM.C1.1, RPB2.12, RPB2.13
unnamed: L.C1.2, L.D1.2, L.R2.1
unnamed: L.C2.+, L.D1.6, L.R5.2, L.R8.1
unnamed: L.D1.1, L.R4.2, L.R5.1, RPB1.13
unnamed: L.D1.3, L.R1.2, L.R3.2, L.R4.1
unnamed: L.D1.5, L.R6.2, L.R7.2
unnamed: L.R2.2, RPB1.11, RPB1.12
unnamed: MS.R2.2, MS.R3.1, RPB1.21
unnamed: PS.VD1.A, XS1.S
unnamed: SB1.NC1, SB1.NC2
V: A.D1.11, B.D1.11, C.D1.11, D.D1.11, E.D1.11, F.D1.11, HL1.A, IO.D1.8, L.D1.8, L.R1.1, L.R6.1, MS.R1.2, PS.C1.+, PS.C2.1, PS.R1.2, PS.VD1.C, SA2.COM1, SA3.COM1, SA3.NC1
VREF: A.D1.3, A.D1.14, A.R2.2, A.R7.2, B.D1.3, B.D1.14, B.R2.2, B.R7.2, C.D1.3, C.D1.14, C.R2.2, C.R7.2, D.D1.3, D.D1.14, D.R2.2, D.R7.2, E.D1.3, E.D1.14, E.R2.2, E.R7.2, F.D1.3, F.D1.14, F.R2.2, F.R7.2, IB.R2.1, IO.D1.5, PS.C3.+, PS.R1.1, PS.R2.2

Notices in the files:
little_angel_chorus_r2a/little_angel_chorus/little_angel_chorus_r2a.kicad_pcb:
This project is licensed under GNU General Public License v3.0 or later
